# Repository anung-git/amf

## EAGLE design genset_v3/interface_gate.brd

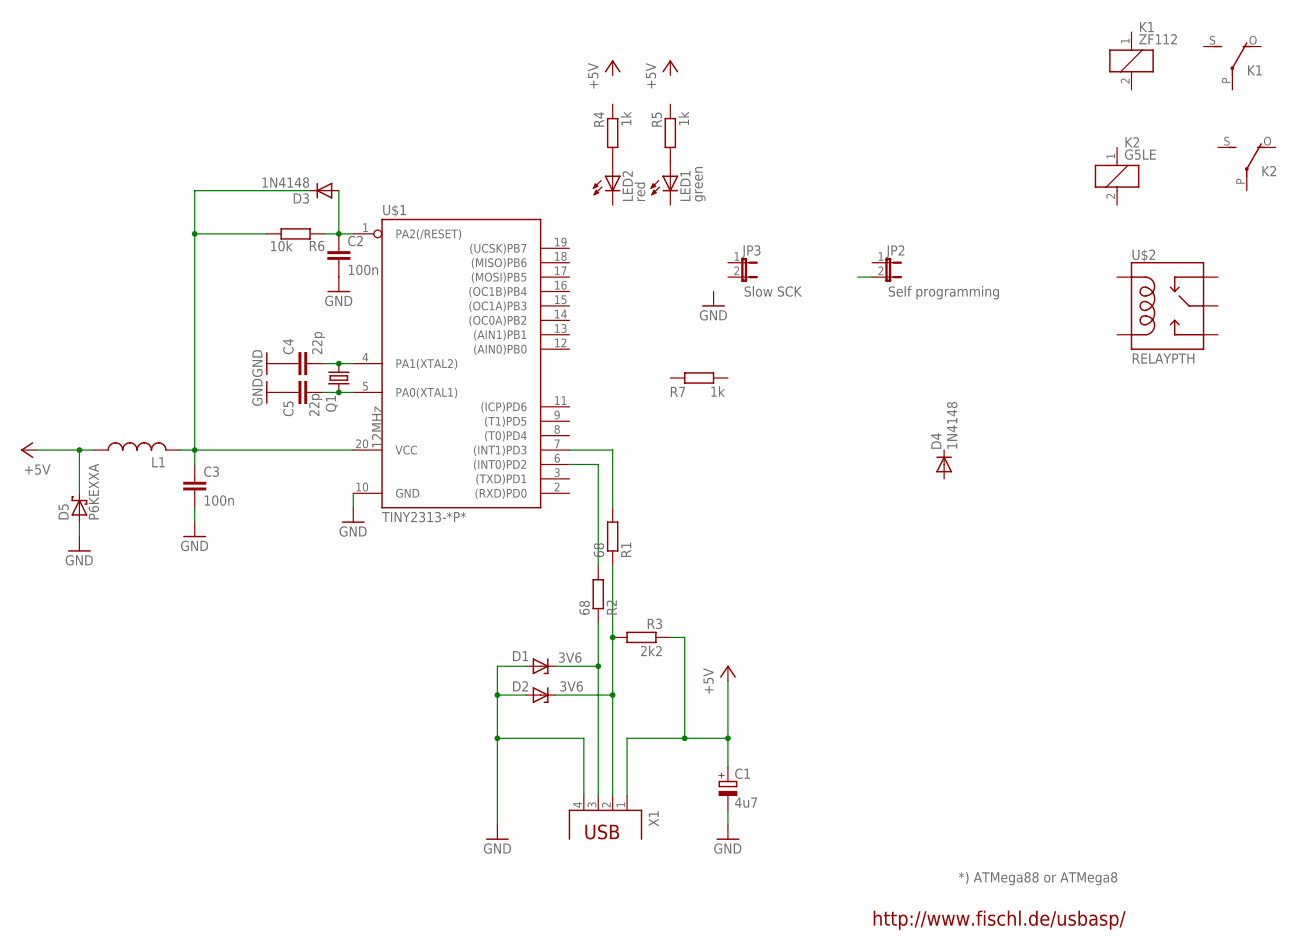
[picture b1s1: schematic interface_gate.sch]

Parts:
C1: 4u7; E2,5-5
C2, C3: 100n; C025-024X044
C4, C5: 22p; C025-024X044
D1, D2: 3V6; DO34Z7
D3, D4: 1N4148; DO35-10
D5: P6KEXXA; C1702-15
JP2: Self programming; JP1
JP3: Slow SCK; JP1
K1: ZF112
K2: G5LE
L1: L-US0207/10; 0207/10
LED1: green; LED3MM
LED2: red; LED3MM
Q1: 12MHz; HC49/S
R1, R2: 68; 0207/10
R3: 2k2; 0207/10
R4, R5, R7: 1k; 0207/10
R6: 10k; 0207/10
U$1: TINY2313-*P*; DIL20
U$2: RELAYPTH; SRD-05VDC-SL-C
X1: PN61729

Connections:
+5V: C1.+, D5.C, L1.1, R3.1, X1.1
GND: C1.-, C2.2, C3.2, C4.1, C5.1, D1.A, D2.A, D5.A, U$1.10 (GND), X1.4
unnamed: C2.1, D3.A, R6.2, U$1.1 (PA2(/RESET))
unnamed: C3.1, D3.C, L1.2, R6.1, U$1.20 (VCC)
unnamed: D2.C, R1.1, R3.2, X1.2
unnamed: R2.2, U$1.6 ((INT0)PD2)
unnamed: D1.C, R2.1, X1.3
unnamed: LED2.A, R4.2
unnamed: R1.2, U$1.7 ((INT1)PD3)
unnamed: C4.2, Q1.2, U$1.4 (PA1(XTAL2))
unnamed: C5.2, Q1.1, U$1.5 (PA0(XTAL1))
unnamed: LED1.A, R5.2

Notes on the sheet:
http://www.fischl.de/usbasp/
*) ATMega88 or ATMega8

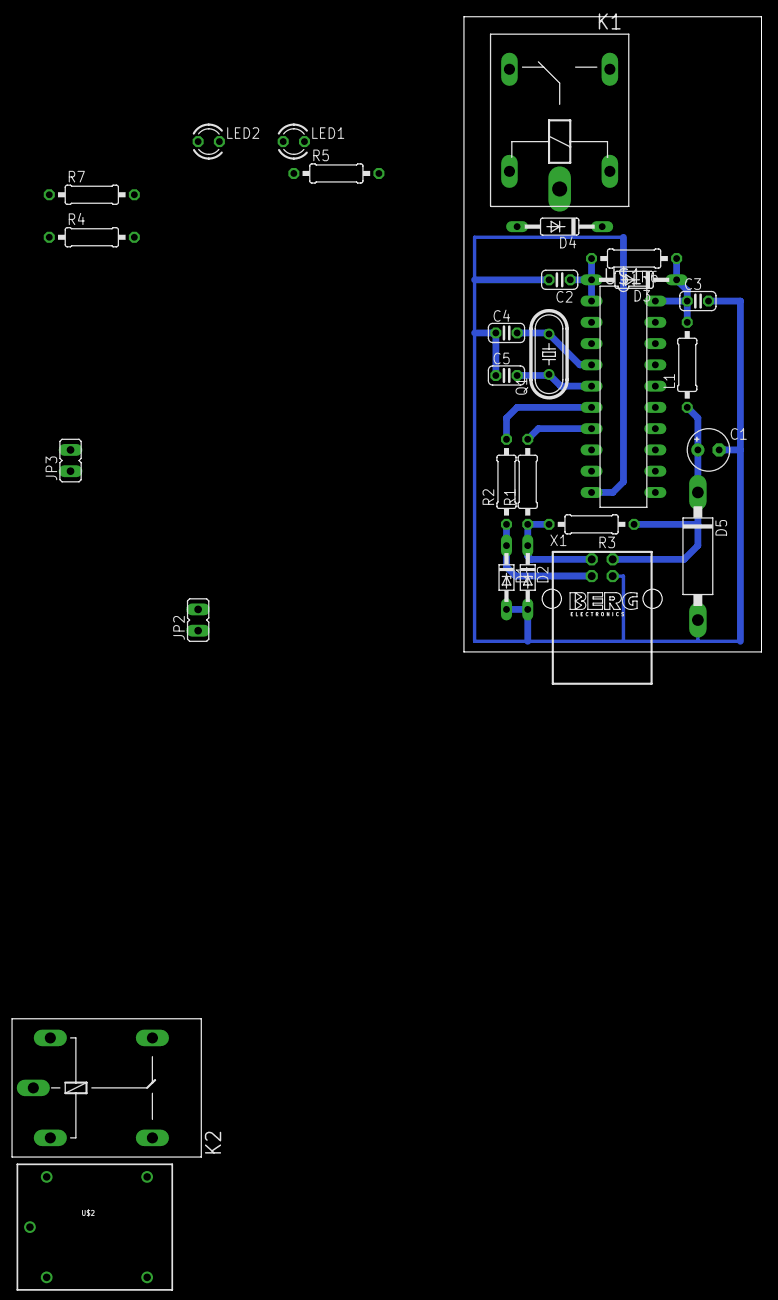
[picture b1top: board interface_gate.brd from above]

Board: 2 copper layers, 35.5 x 75.9 mm, 28 parts (0 on the bottom side), 12 nets.

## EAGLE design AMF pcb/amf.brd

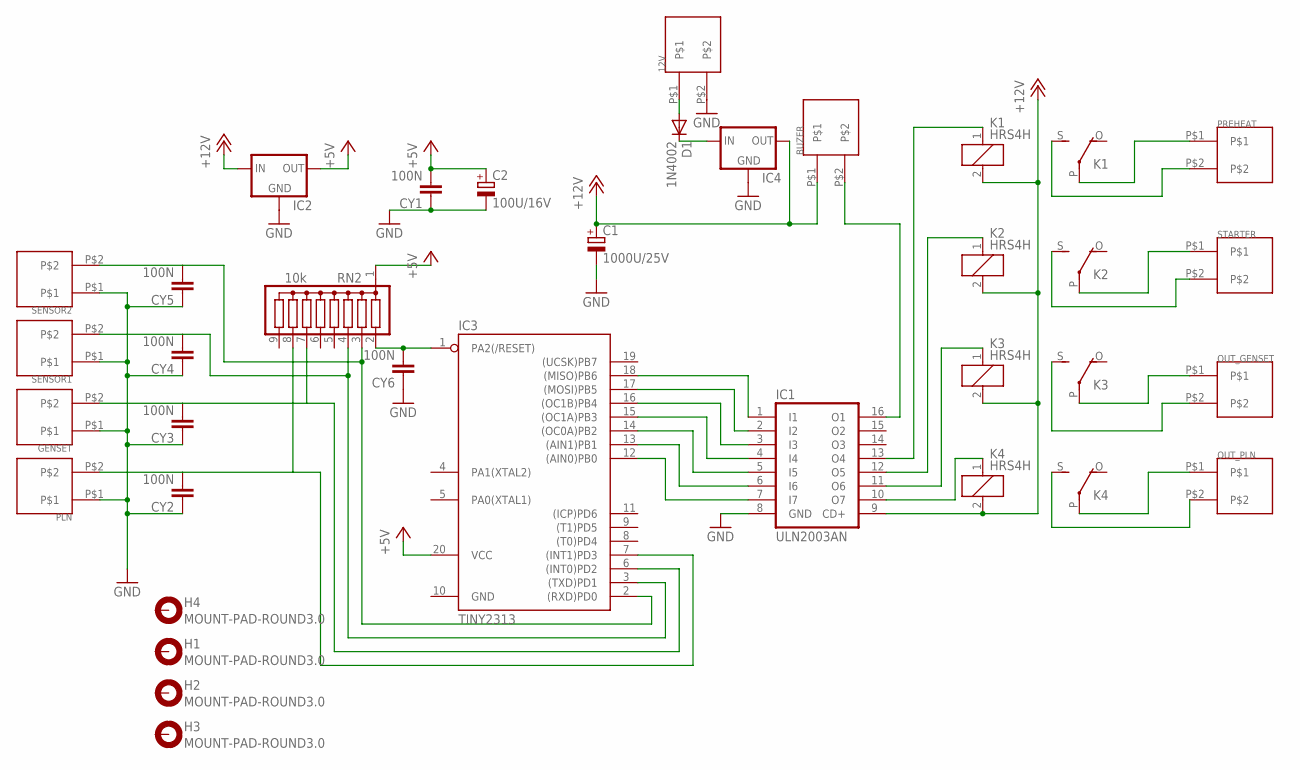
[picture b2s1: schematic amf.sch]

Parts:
12V: TERMINAL-2U-5MM
BUZER: TERMINAL-2U-5MM
C1: 1000U/25V; E5-10,5
C2: 100U/16V; E2,5-5
CY1, CY2, CY3, CY4, CY5, CY6: 100N; YC7B5
D1: 1N4002; DO35-10
GENSET: TERMINAL-2U-5MM
H1, H2, H3, H4: MOUNT-PAD-ROUND3.0; 3,0-PAD
IC1: ULN2003AN; DIL16
IC2, IC4: 78XXS
IC3: TINY2313; DIL20
K1, K2, K3, K4: HRS4H; ZF112
OUT_GENSET: TERMINAL-2U-5MM
OUT_PLN: TERMINAL-2U-5MM
PLN: TERMINAL-2U-5MM
PREHEAT: TERMINAL-2U-5MM
RN2: 10k; SIL9
SENSOR1, SENSOR2: TERMINAL-2U-5MM
STARTER: TERMINAL-2U-5MM

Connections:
+5V: C2.+, CY1.2, IC2.OUT, IC3.20 (VCC), RN2.1
+12V: BUZER.P$1, C1.+, IC1.9 (CD+), IC2.IN, IC4.OUT, K1.2, K2.2, K3.2, K4.2
GND: 12V.P$2, C1.-, C2.-, CY1.1, CY2.1, CY3.1, CY4.1, CY5.1, CY6.1, GENSET.P$1, IC1.8 (GND), IC2.GND, IC3.10 (GND), IC4.GND, PLN.P$1, SENSOR1.P$1, SENSOR2.P$1
unnamed: 12V.P$1, D1.A
unnamed: D1.C, IC4.IN
unnamed: IC1.10 (O7), K4.1
unnamed: IC1.11 (O6), K3.1
unnamed: IC1.12 (O5), K2.1
unnamed: IC1.13 (O4), K1.1
unnamed: IC1.7 (I7), IC3.12 ((AIN0)PB0)
unnamed: IC1.6 (I6), IC3.13 ((AIN1)PB1)
unnamed: IC1.5 (I5), IC3.14 ((OC0A)PB2)
unnamed: IC1.4 (I4), IC3.15 ((OC1A)PB3)
unnamed: IC1.3 (I3), IC3.16 ((OC1B)PB4)
unnamed: IC1.2 (I2), IC3.17 ((MOSI)PB5)
unnamed: IC1.1 (I1), IC3.18 ((MISO)PB6)
unnamed: K4.P, OUT_PLN.P$1
unnamed: K3.P, OUT_GENSET.P$1
unnamed: K4.S, OUT_PLN.P$2
unnamed: K3.S, OUT_GENSET.P$2
unnamed: K2.P, STARTER.P$1
unnamed: K2.S, STARTER.P$2
unnamed: K1.P, PREHEAT.P$1
unnamed: K1.S, PREHEAT.P$2
unnamed: CY4.2, IC3.3 ((TXD)PD1), RN2.4, SENSOR1.P$2
unnamed: BUZER.P$2, IC1.16 (O1)
unnamed: CY5.2, IC3.2 ((RXD)PD0), RN2.3, SENSOR2.P$2
unnamed: CY6.2, IC3.1 (PA2(/RESET)), RN2.2
unnamed: CY3.2, GENSET.P$2, IC3.6 ((INT0)PD2), RN2.7
unnamed: CY2.2, IC3.7 ((INT1)PD3), PLN.P$2, RN2.8

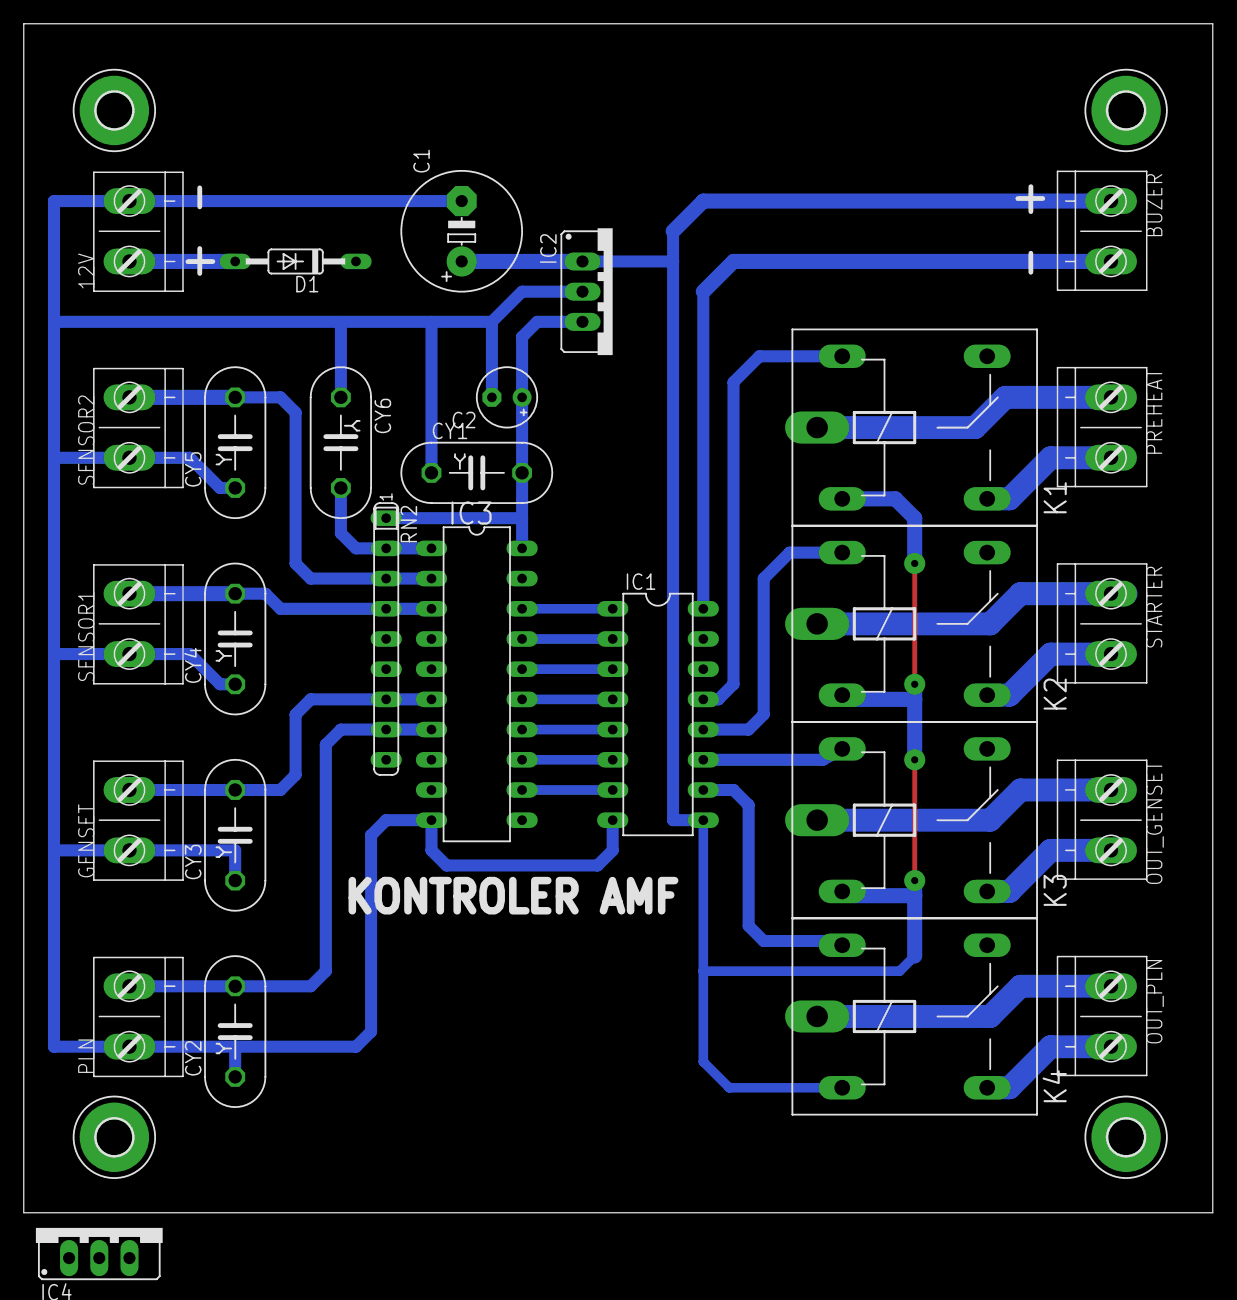
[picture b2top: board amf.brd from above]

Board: 2 copper layers, 100.0 x 100.0 mm, 32 parts (0 on the bottom side), 30 nets.

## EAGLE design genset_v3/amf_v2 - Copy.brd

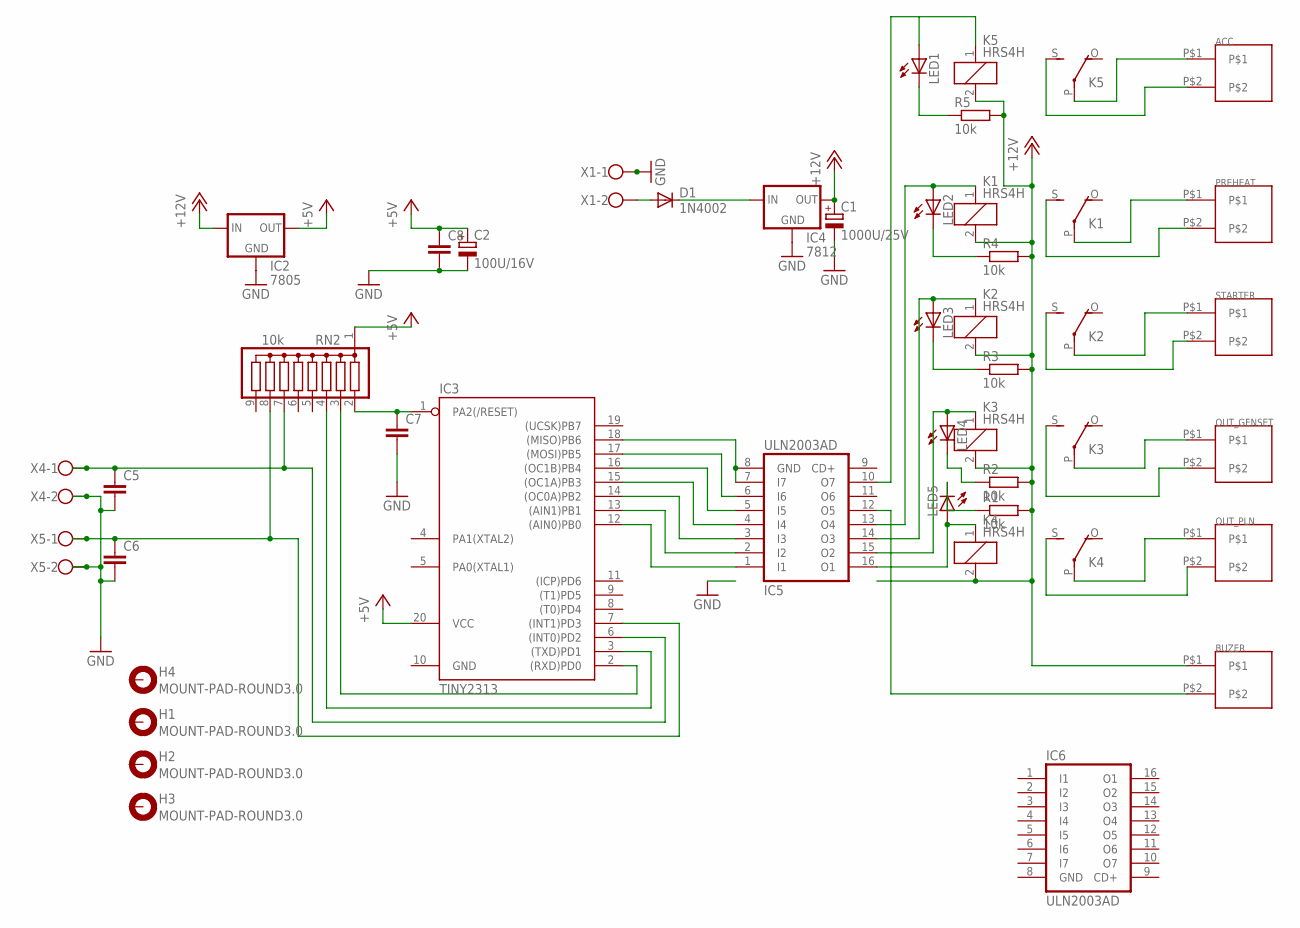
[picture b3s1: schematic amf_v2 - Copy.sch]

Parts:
ACC: TERMINAL-2U-5MM
BUZER: TERMINAL-2U-5MM
C1: 1000U/25V; E5-10,5
C2: 100U/16V; E2,5-5
C5, C6, C7, C8: C-EU075-032X103; C075-032X103
D1: 1N4002; DO35-10
H1, H2, H3, H4: MOUNT-PAD-ROUND3.0; 3,0-PAD
IC2: 7805; 78XXS
IC3: TINY2313; DIL20
IC4: 7812; 78XXS
IC5, IC6: ULN2003AD; SO16
K1, K2, K3, K4, K5: HRS4H; ZF112
LED1, LED2, LED3, LED4, LED5: LED5MM
OUT_GENSET: TERMINAL-2U-5MM
OUT_PLN: TERMINAL-2U-5MM
PREHEAT: TERMINAL-2U-5MM
R1, R2, R3, R4, R5: 10k; 0204V
RN2: 10k; SIL9
STARTER: TERMINAL-2U-5MM
X1, X4, X5: W237-102

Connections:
+5V: C2.+, C8.1, IC2.OUT, IC3.20 (VCC), RN2.1
+12V: BUZER.P$1, C1.+, IC2.IN, IC4.OUT, K1.2, K2.2, K3.2, K4.2, K5.2, R1.2, R2.2, R3.2, R4.2, R5.2
GND: C1.-, C2.-, C5.2, C6.2, C7.2, C8.2, IC2.GND, IC3.10 (GND), IC4.GND, IC6.8 (GND), X1.1, X4.2, X5.2
unnamed: D1.A, X1.2
unnamed: D1.C, IC4.IN
unnamed: IC5.16 (O1), K4.1, LED5.A
unnamed: IC5.15 (O2), K3.1, LED4.A
unnamed: IC5.14 (O3), K2.1, LED3.A
unnamed: IC5.13 (O4), K1.1, LED2.A
unnamed: IC3.12 ((AIN0)PB0), IC5.1 (I1)
unnamed: IC3.13 ((AIN1)PB1), IC5.2 (I2)
unnamed: IC3.14 ((OC0A)PB2), IC5.3 (I3)
unnamed: IC3.15 ((OC1A)PB3), IC5.4 (I4)
unnamed: IC3.16 ((OC1B)PB4), IC5.5 (I5)
unnamed: IC3.17 ((MOSI)PB5), IC5.6 (I6)
unnamed: IC3.18 ((MISO)PB6), IC5.7 (I7), IC5.8 (GND)
unnamed: K4.P, OUT_PLN.P$1
unnamed: K3.P, OUT_GENSET.P$1
unnamed: K4.S, OUT_PLN.P$2
unnamed: K3.S, OUT_GENSET.P$2
unnamed: K2.P, STARTER.P$1
unnamed: K2.S, STARTER.P$2
unnamed: K1.P, PREHEAT.P$1
unnamed: K1.S, PREHEAT.P$2
unnamed: IC3.3 ((TXD)PD1), RN2.4
unnamed: IC5.10 (O7), K5.1, LED1.A
unnamed: ACC.P$1, K5.P
unnamed: ACC.P$2, K5.S
unnamed: IC3.2 ((RXD)PD0), RN2.3
unnamed: C7.1, IC3.1 (PA2(/RESET)), RN2.2
unnamed: C5.1, IC3.6 ((INT0)PD2), RN2.7, X4.1
unnamed: C6.1, IC3.7 ((INT1)PD3), RN2.8, X5.1
unnamed: BUZER.P$2, IC5.12 (O5)
unnamed: LED1.K (C), R5.1
unnamed: LED2.K (C), R4.1
unnamed: LED3.K (C), R3.1
unnamed: LED4.K (C), R2.1
unnamed: LED5.K (C), R1.1

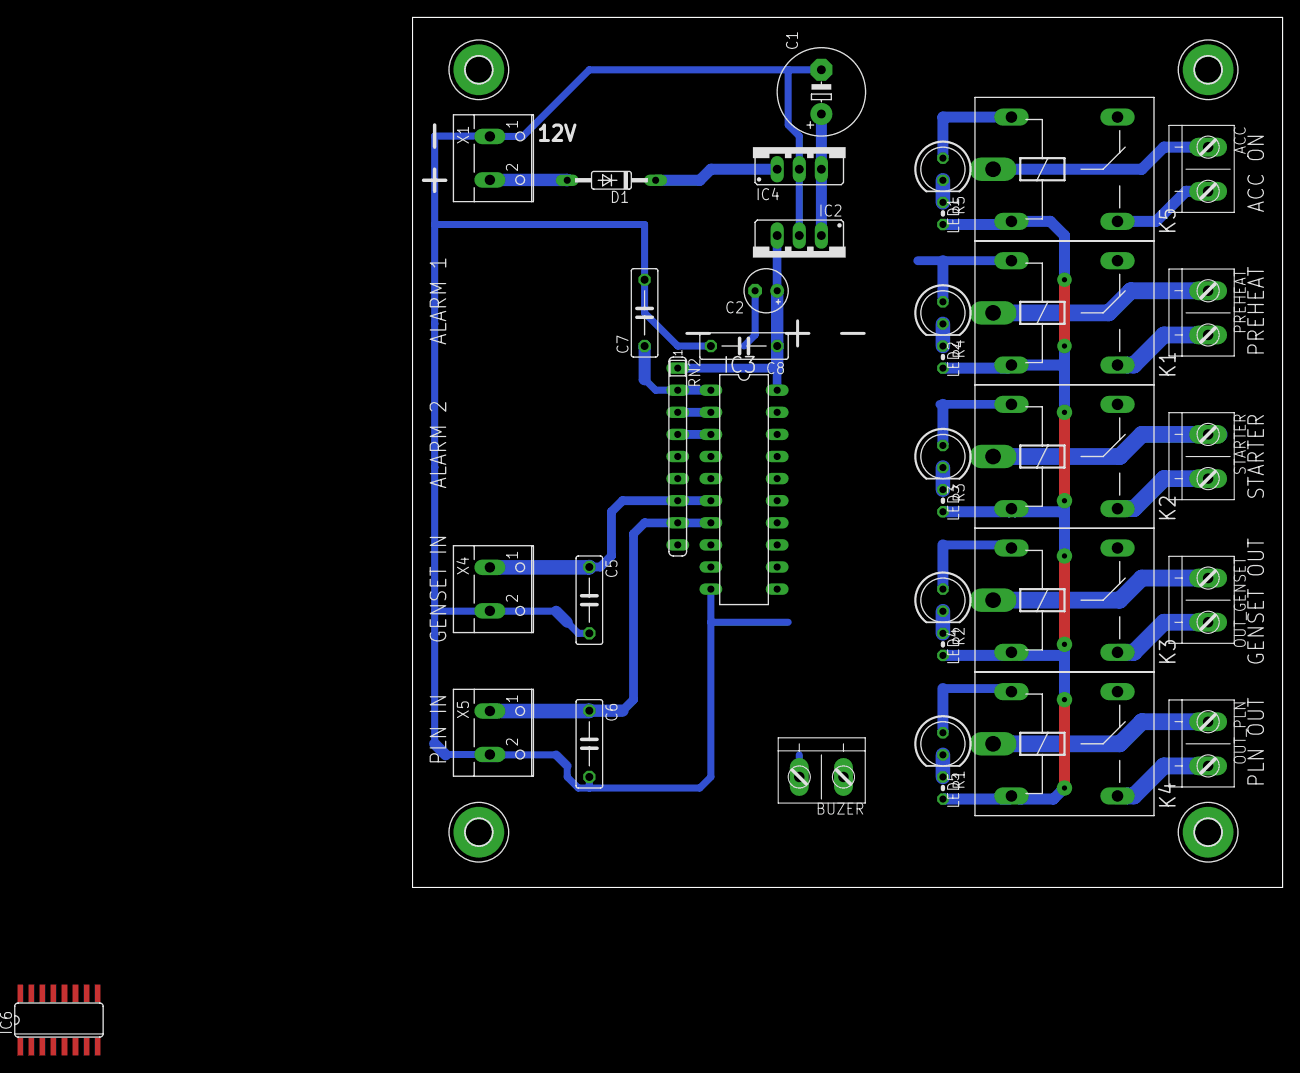
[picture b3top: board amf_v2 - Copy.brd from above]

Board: 2 copper layers, 100.0 x 100.0 mm, 41 parts (1 on the bottom side), 38 nets.

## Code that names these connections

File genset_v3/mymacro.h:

#include <avr/wdt.h>
#include <avr/io.h>
#include <util/delay.h>
#include <compat/deprecated.h>

#define port_sensor1		PORTD
#define pin_sensor1			PIND
#define ddr_sensor1			DDRD
#define bit_sensor1			PD0

#define port_sensor2		PORTD
#define pin_sensor2			PIND
#define ddr_sensor2			DDRD
#define bit_sensor2			PD1

#define port_genset_in		PORTD
#define pin_genset_in		PIND
#define ddr_genset_in		DDRD
#define bit_genset_in		PD2

#define port_pln_in			PORTD
#define pin_pln_in			PIND
#define ddr_pln_in			DDRD
#define bit_pln_in			PD3

#define port_buzer			PORTB
#define ddr_buzer			DDRB
#define bit_buzer			PB4

#define port_acc			PORTB
#define ddr_acc				DDRB
#define bit_acc				PB6

#define port_preheat		PORTB
#define ddr_preheat			DDRB
#define bit_preheat			PB3

#define port_starter		PORTB
#define ddr_starter			DDRB
#define bit_starter			PB2

#define port_genset_out		PORTB
#define ddr_genset_out		DDRB
#define bit_genset_out		PB1

#define port_pln_out		PORTB
#define ddr_pln_out			DDRB
#define bit_pln_out			PB0


#define x1_lo()				port_sensor1&=~_BV(bit_sensor1)
#define x1_hi()				port_sensor1|=_BV(bit_sensor1)
#define x1_in()				ddr_sensor1&=~_BV(bit_sensor1)
#define r_x1()				bit_is_set(pin_sensor1,bit_sensor1)
#define x2_lo()				port_sensor2&=~_BV(bit_sensor2)
#define x2_hi()				port_sensor2|=_BV(bit_sensor2)
#define x2_in()				ddr_sensor2&=~_BV(bit_sensor2)
#define r_x2()				bit_is_set(pin_sensor2,bit_sensor2)
#define x3_lo()				port_genset_in&=~_BV(bit_genset_in)
#define x3_hi()				port_genset_in|=_BV(bit_genset_in)
#define x3_in()				ddr_genset_in&=~_BV(bit_genset_in)
#define r_x3()				bit_is_set(pin_genset_in,bit_genset_in)
#define x4_lo()				port_pln_in	&=~_BV(bit_pln_in)
#define x4_hi()				port_pln_in	|=_BV(bit_pln_in)
#define x4_in()				ddr_pln_in&=~_BV(bit_pln_in)
#define r_x4()				bit_is_set(pin_pln_in,bit_pln_in)

#define y1_lo()				port_acc&=~_BV(bit_acc)
#define y1_hi()				port_acc|=_BV(bit_acc)
#define y1_out()			ddr_acc|=_BV(bit_acc)
#define y2_lo()				port_preheat&=~_BV(bit_preheat)
#define y2_hi()				port_preheat|=_BV(bit_preheat)
#define y2_out()			ddr_preheat|=_BV(bit_preheat)
#define y3_lo()				port_starter&=~_BV(bit_starter)
#define y3_hi()				port_starter|=_BV(bit_starter)
#define y3_out()			ddr_starter|=_BV(bit_starter)
#define y4_lo()				port_genset_out&=~_BV(bit_genset_out)
#define y4_hi()				port_genset_out|=_BV(bit_genset_out)
#define y4_out()			ddr_genset_out|=_BV(bit_genset_out)
#define y5_lo()				port_pln_out&=~_BV(bit_pln_out)
#define y5_hi()				port_pln_out|=_BV(bit_pln_out)
#define y5_out()			ddr_pln_out	|=_BV(bit_pln_out)
#define y6_lo()				port_buzer&=~_BV(bit_buzer)
#define y6_hi()				port_buzer|=_BV(bit_buzer)
#define y6_out()			ddr_buzer|=_BV(bit_buzer)

/*
x1 = sensor 1
x2 = sensor 2
x3 = sensor genset
x4 = sensor pln

y1 = acc on
y2 = preheat
y3 = starter
y4 = genset
y5 = pln
y6 = buzer
*/

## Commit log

2019-06-11 upload file
2019-06-11 hapus backup pcb
